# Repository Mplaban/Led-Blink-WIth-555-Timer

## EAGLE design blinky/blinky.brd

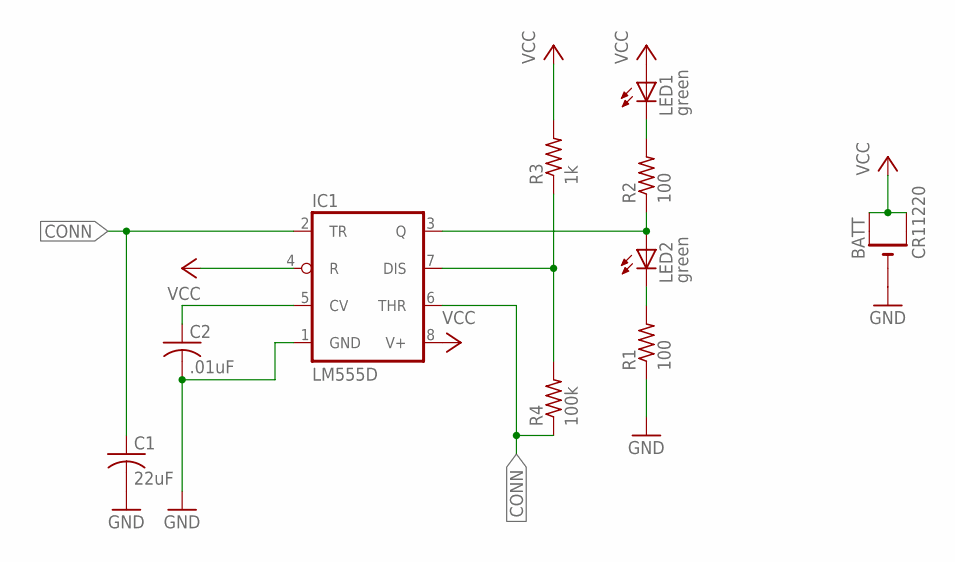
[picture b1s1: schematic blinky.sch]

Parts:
BATT: CR11220; CR1220-SMD
C1: 22uF; C0805
C2: .01uF; C0805
IC1: LM555D; SO08
LED1, LED2: green; CHIPLED_0805
R1, R2: 100; R0805
R3: 1k; R0805
R4: 100k; R0805

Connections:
CONN: C1.1, IC1.2 (TR), IC1.6 (THR), R4.1
GND: BATT.-, C1.2, C2.2, IC1.1 (GND), R1.1
unnamed: LED1.C, R2.2
unnamed: IC1.3 (Q), LED2.A, R2.1
unnamed: LED2.C, R1.2
unnamed: IC1.7 (DIS), R3.1, R4.2
unnamed: C2.1, IC1.5 (CV)
VCC: BATT.+$1 (+), BATT.+$2 (+1), IC1.4 (R), IC1.8 (V+), LED1.A, R3.2

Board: 2 copper layers, 11 parts (0 on the bottom side), 8 nets, no tracks yet.

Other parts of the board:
DRILEGEND: DRILEGEND
